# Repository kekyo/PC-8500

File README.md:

# NEC PC-8500 hacking

NEC PC-8500 is an older laptop CP/M-80 computer, last model on [PC-8200 (ja)](https://ja.wikipedia.org/wiki/PC-8200%E3%82%B7%E3%83%AA%E3%83%BC%E3%82%BA) series (OEM versioned: [Tandy RadioShack Model 100](https://en.wikipedia.org/wiki/TRS-80_Model_100))

I bought it, but does not exist any information at all... I begin recording about tech information on this repo.

----

## Replace memory backup battery

Memory backup battery maybe dead in 2021.
You can replace it located at below photo.

* Parts number: `GB250H-3`, but I couldn't find same battery.
* I replaced with 006P 9V NiMH battery with snap connector. Because it's popular battery form and easy to get.
  * CAUTION: You MUST replace with ONLY RECHARGEABLE battery.
  * CAUTION: You MUST DISCHARGE LOWER THAN 5V before connect. The battery backup voltage is 5V.

----

## Replace masked rom

[PC-8500 Masked rom riser PCB (Eagle CAD)](./pc8500romriser/)

----
## License

MIT (made by hand) or imported depending library supplier.

Supplier list:

* [Ultra Librarian](https://www.ultralibrarian.com/)
* [Snap EDA](https://www.snapeda.com/home/)

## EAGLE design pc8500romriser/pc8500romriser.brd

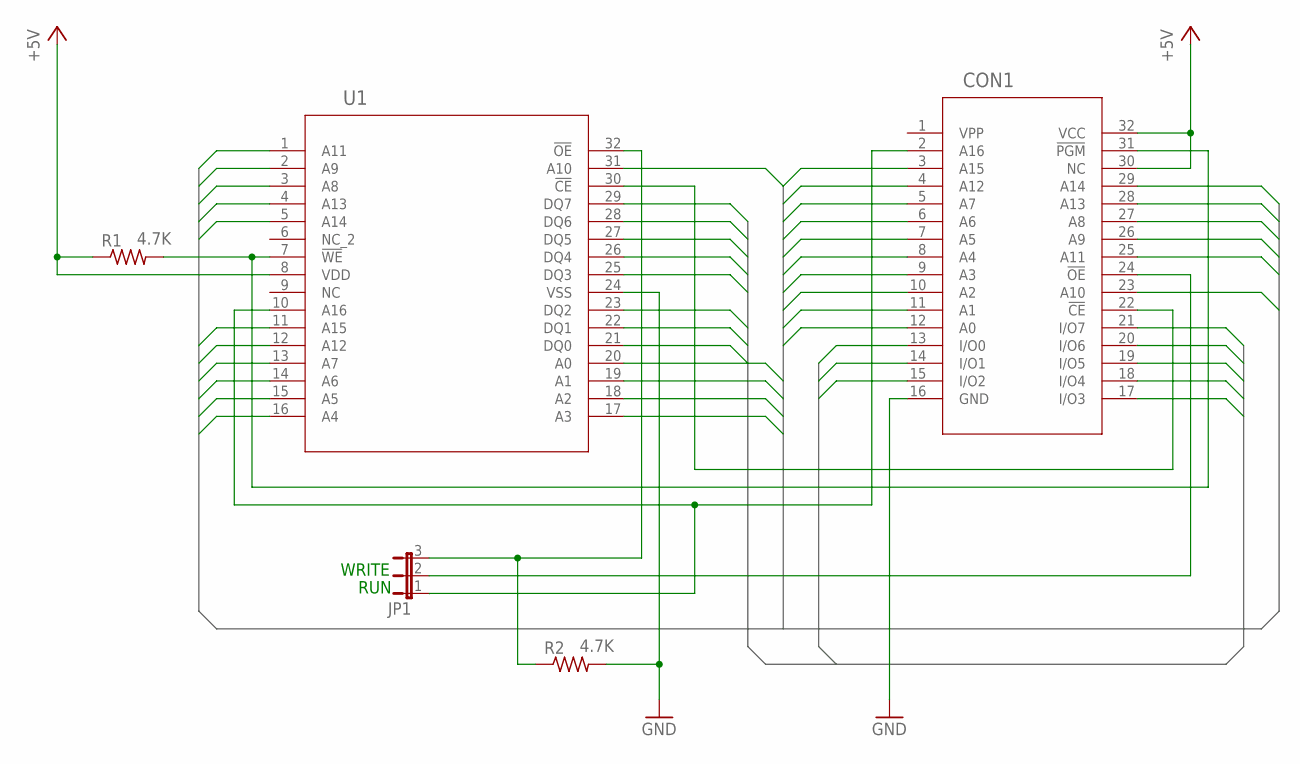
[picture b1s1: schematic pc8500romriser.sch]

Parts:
CON1: HN27C101AG
JP1: JP2E; JP2
R1, R2: 4.7K; R2010
U1: SST39VF010-70-4I-WHETSOP32_WH_SST_MCH-M; TSOP32_WH_SST_MCH-M

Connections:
+5V: CON1.30 (NC), CON1.32 (VCC), R1.1, U1.8 (VDD)
/CE: CON1.22 (!CE), U1.30 (!CE)
/OE: JP1.3, R2.1, U1.32 (!OE)
/WE: CON1.31 (!PGM), R1.2, U1.7 (!WE)
A0: CON1.12 (A0), U1.20 (A0)
A1: CON1.11 (A1), U1.19 (A1)
A2: CON1.10 (A2), U1.18 (A2)
A3: CON1.9 (A3), U1.17 (A3)
A4: CON1.8 (A4), U1.16 (A4)
A5: CON1.7 (A5), U1.15 (A5)
A6: CON1.6 (A6), U1.14 (A6)
A7: CON1.5 (A7), U1.13 (A7)
A8: CON1.27 (A8), U1.3 (A8)
A9: CON1.26 (A9), U1.2 (A9)
A10: CON1.23 (A10), U1.31 (A10)
A11: CON1.25 (A11), U1.1 (A11)
A12: CON1.4 (A12), U1.12 (A12)
A13: CON1.28 (A13), U1.4 (A13)
A14: CON1.29 (A14), U1.5 (A14)
A15: CON1.3 (A15), U1.11 (A15)
A16: CON1.2 (A16), JP1.1, U1.10 (A16)
A16/OE: CON1.24 (!OE), JP1.2
D0: CON1.13 (I/O0), U1.21 (DQ0)
D1: CON1.14 (I/O1), U1.22 (DQ1)
D2: CON1.15 (I/O2), U1.23 (DQ2)
D3: CON1.17 (I/O3), U1.25 (DQ3)
D4: CON1.18 (I/O4), U1.26 (DQ4)
D5: CON1.19 (I/O5), U1.27 (DQ5)
D6: CON1.20 (I/O6), U1.28 (DQ6)
D7: CON1.21 (I/O7), U1.29 (DQ7)
GND: CON1.16 (GND), R2.2, U1.24 (VSS)
VPP: CON1.1 (VPP)

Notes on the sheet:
RUN
WRITE

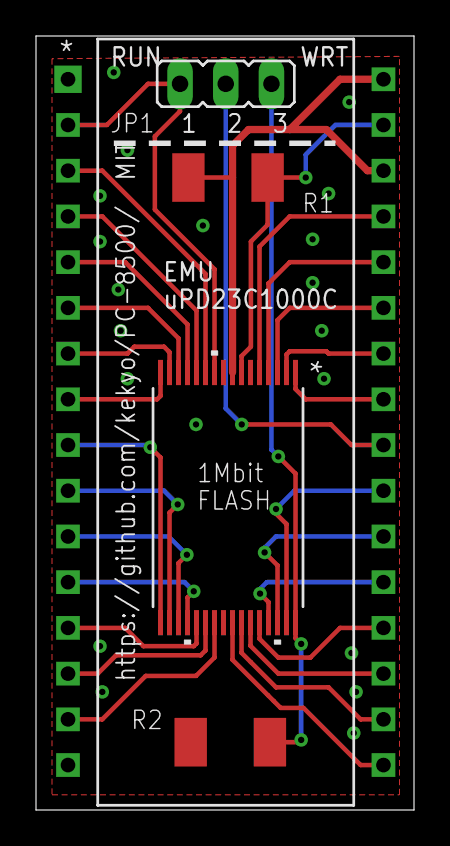
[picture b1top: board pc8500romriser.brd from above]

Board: 2 copper layers, 21.0 x 43.0 mm, 5 parts (0 on the bottom side), 31 nets.

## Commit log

2021-09-03 Adjusted routing signal lines.

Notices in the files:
parts and their libraries:
COPYRIGHT: Copyright (C) 2021 Ultra Librarian. All rights reserved.
